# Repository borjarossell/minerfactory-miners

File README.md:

minerfactory-miners
===================
Minerfactory custom design Bitcoin ASIC miners using the BITFURY ASIC chip.
The project includes the Eagle CAD .brd and .sch board and schematic files for each board. No gerber files included.

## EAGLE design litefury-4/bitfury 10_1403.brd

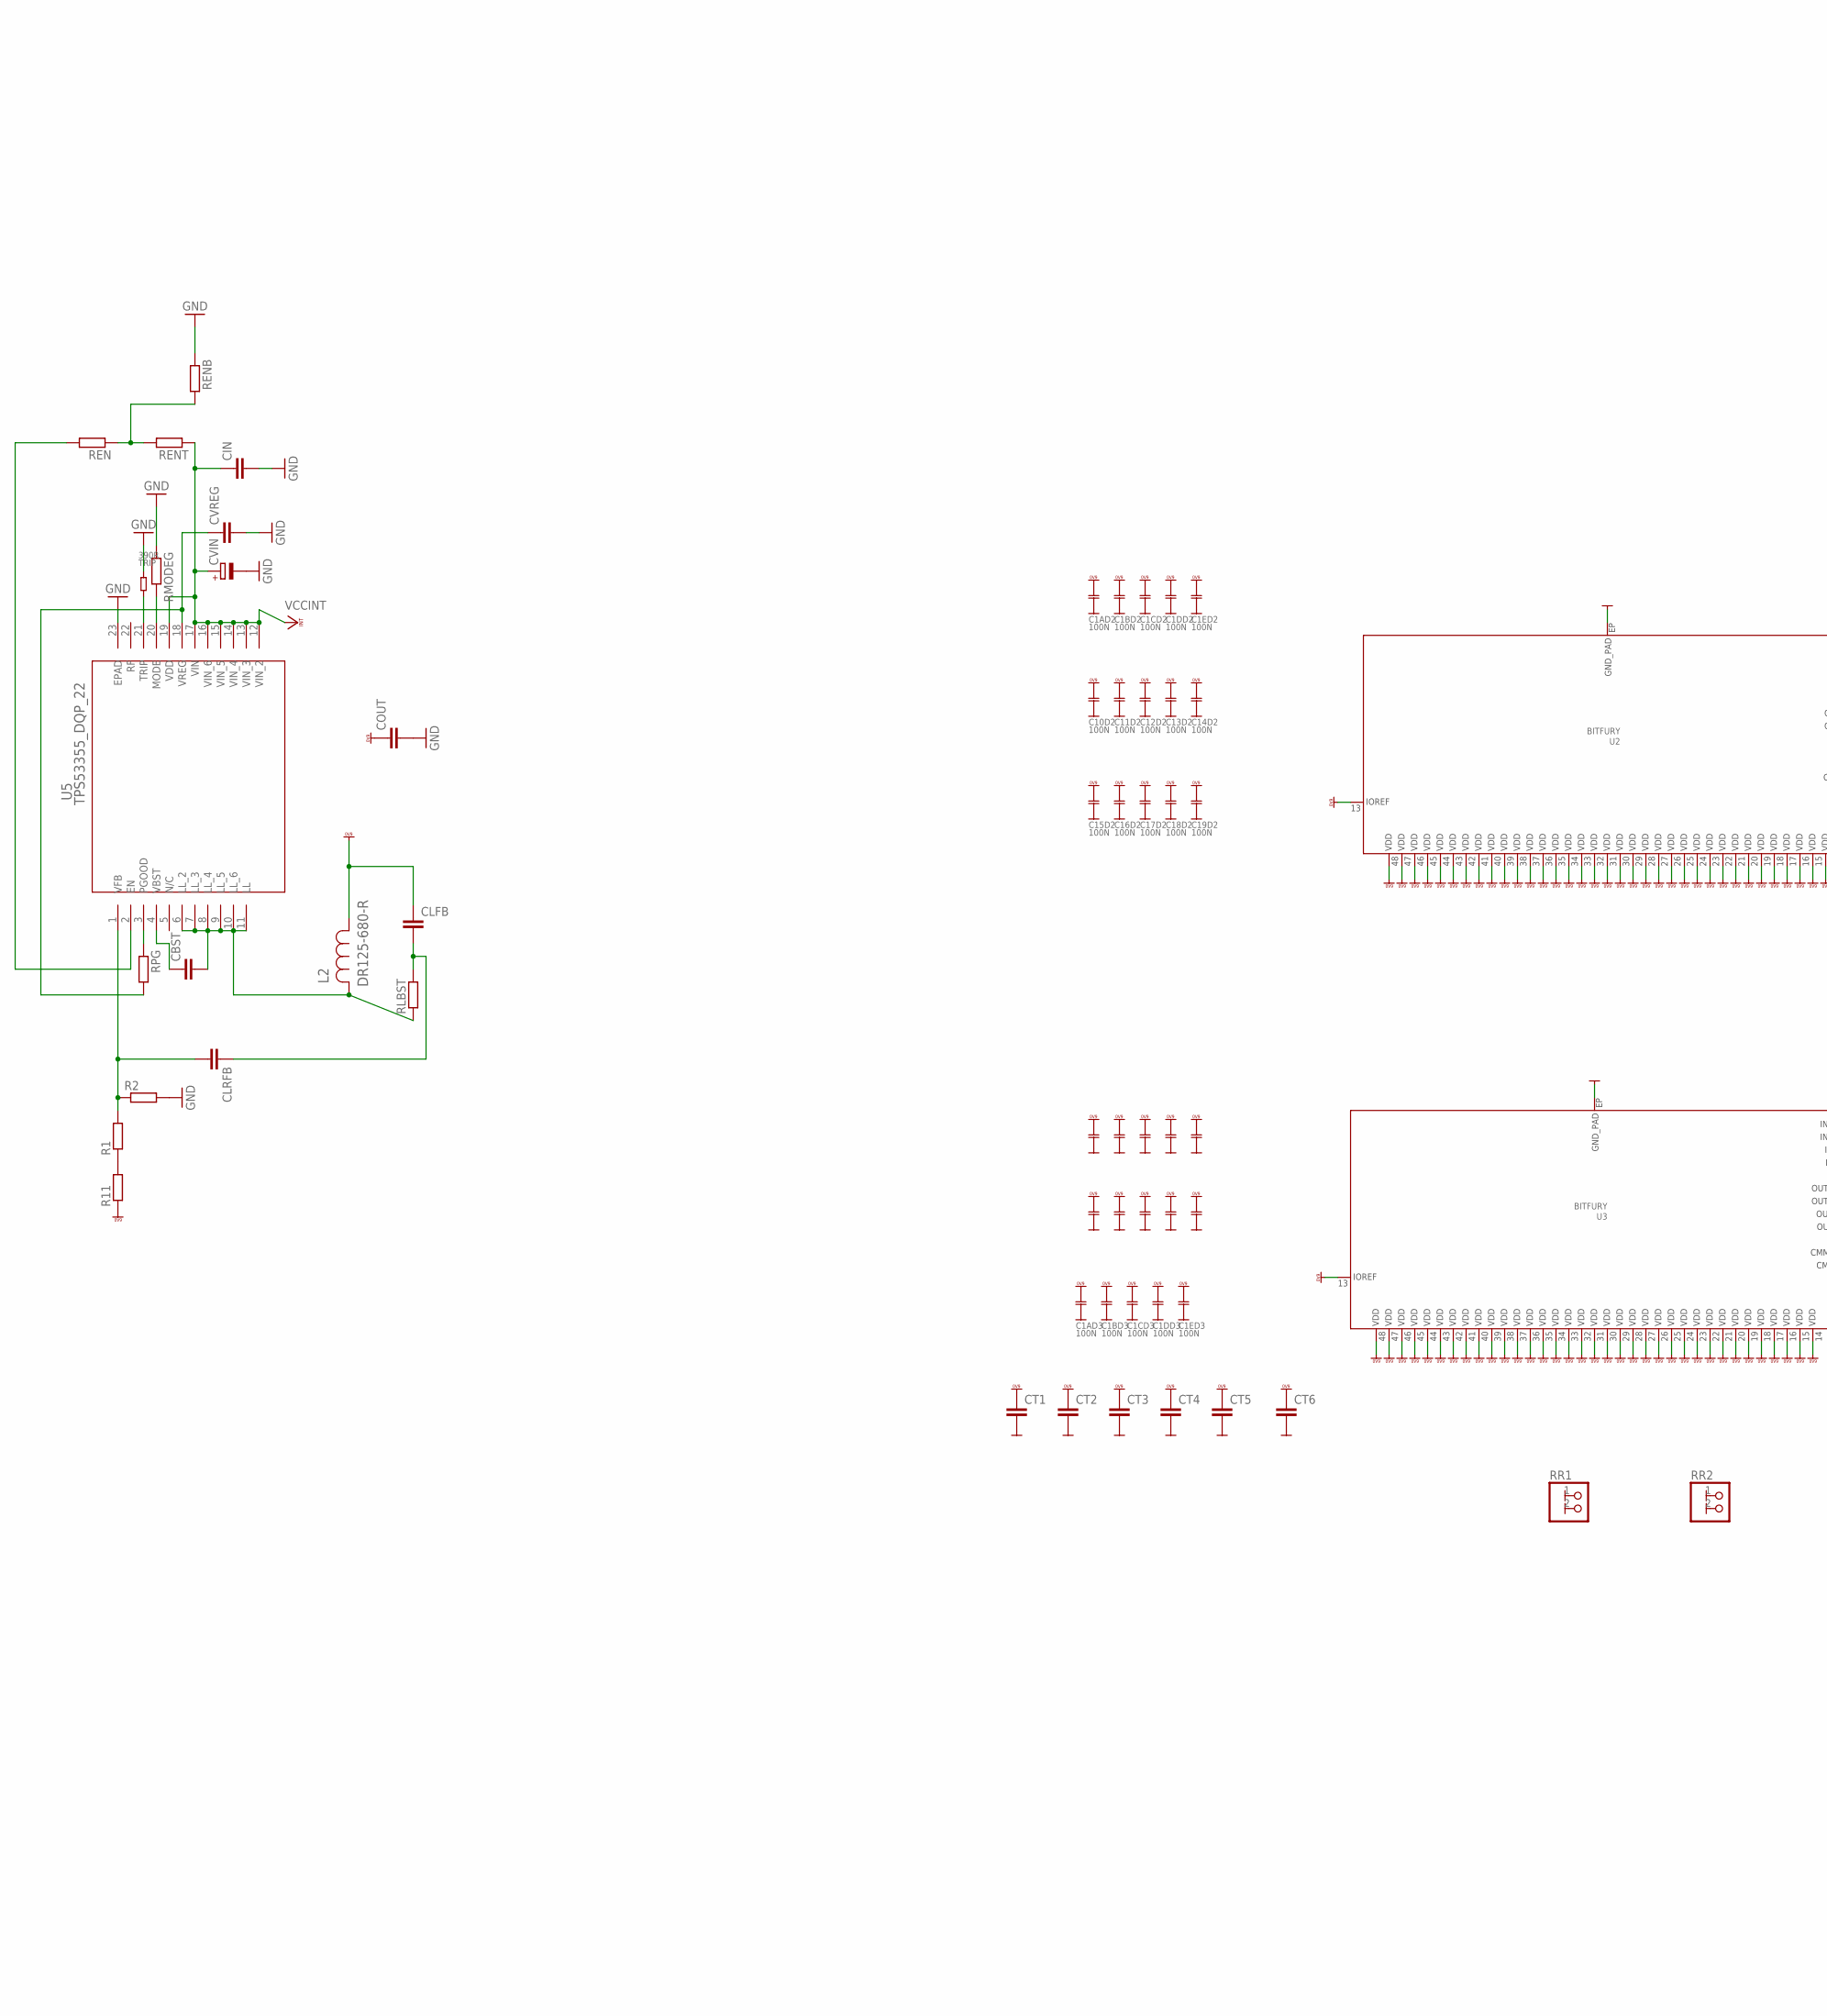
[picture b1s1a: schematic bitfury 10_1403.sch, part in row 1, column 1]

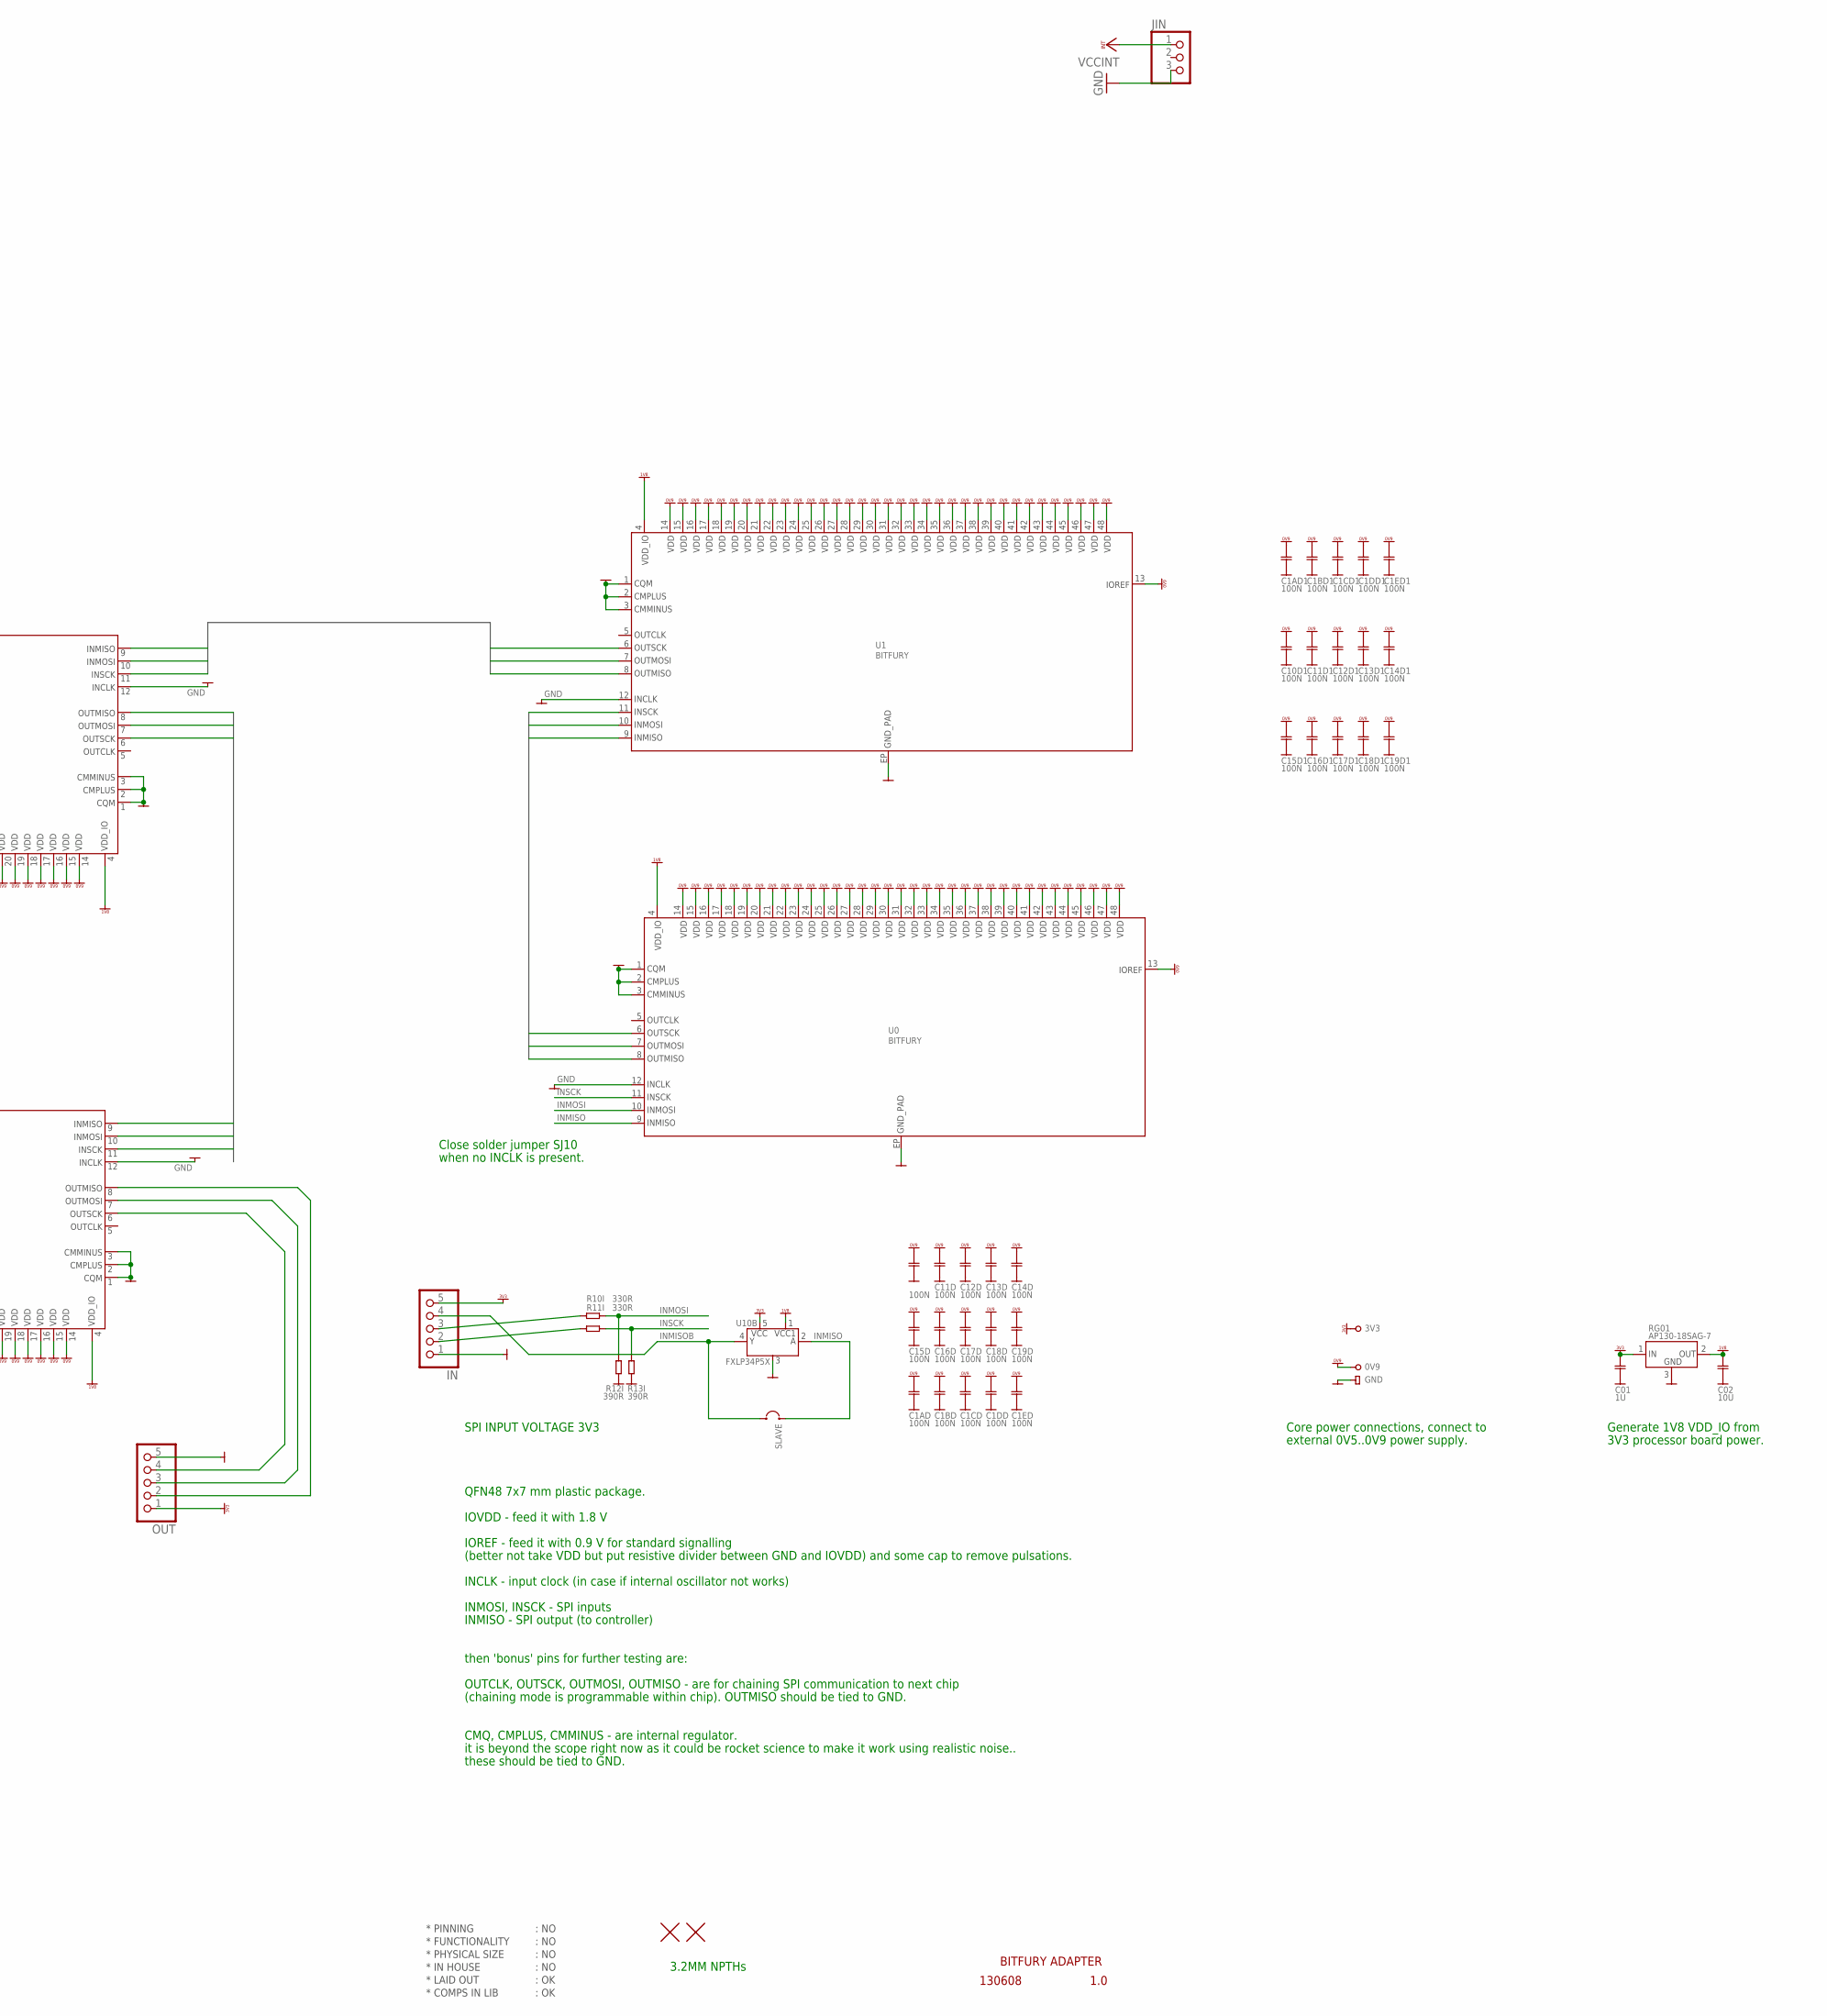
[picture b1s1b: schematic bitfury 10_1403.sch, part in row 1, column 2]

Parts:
0V9, 3V3: PIN_TEST_BIG; PAD_HOLE_BIG
C01: 1U; CAP0603
C1AD, C1AD1, C1AD2, C1AD3, C1BD, C1BD1, C1BD2, C1BD3, C1CD, C1CD1, C1CD2, C1CD3, C1DD, C1DD1, C1DD2, C1DD3, C1ED, C1ED1, C1ED2, C1ED3, C10D, C10D1, C10D2, C10D3, C11D, C11D1, C11D2, C11D3, C12D, C12D1, C12D2, C12D3, C13D, C13D1, C13D2, C13D3, C14D, C14D1, C14D2, C14D3, C15D, C15D1, C15D2, C15D3, C16D, C16D1, C16D2, C16D3, C17D, C17D1, C17D2, C17D3, C18D, C18D1, C18D2, C18D3, C19D, C19D1, C19D2, C19D3: 100N; CAP0402
C02: 10U; CAP0603
CBST: C-EUC0805; C0805
CIN: C-EUC1210; C1210
CLFB: C-EUC0805; C0805
CLRFB: C-EUC0805; C0805
COUT: C-EUC1210; C1210
CT1, CT2, CT3, CT4, CT5, CT6: C-EUC1206; C1206
CVIN: CPOL-EU153CLV-0505; 153CLV-0505
CVREG: C-EUC0603; C0603
H1, H2: HOLE_NPTH_3.2MM
IN: PINHD-1X5/90; 1X05/90
JIN: PINHD-1X3; 1X03
L2: DR125-680-R; INDM125125X600N
OUT: PINHD-1X5/90; 1X05/90
R1, R2, R11: R-EU_R0603; R0603
R10I, R11I: 330R; RES0603
R12I, R13I: 390R; RES0603
REN: R-EU_R0603; R0603
RENB: R-EU_R0603; R0603
RENT: R-EU_R0603; R0603
RG01: AP130-18SAG-7; SOT23
RLBST: R-EU_R0603; R0603
RMODEG: R-EU_R0603; R0603
RPG: R-EU_R0603; R0603
RR1, RR2: PINHD-1X2/90; 1X02/90
SLAVE: SJ2SJ2-S; SJ2-S
TRIP: 390R; RES0603
U0, U1, U2, U3: BITFURY; QNF48
U5: TPS53355_DQP_22; DQP22_5P479X3P24
U10B: FXLP34P5X; SOT23-5
U$83: PIN_GND; PAD_HOLE_SQR_1.8MM

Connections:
B1B2C1: U0.6 (6.OUTSCK), U1.11 (11.INSCK)
B1B2C2: U0.7 (7.OUTMOSI), U1.10 (10.INMOSI)
B1B2C3: U0.8 (8.OUTMISO), U1.9 (9.INMISO)
B2B3C1: U1.6 (6.OUTSCK), U2.11 (11.INSCK)
B2B3C2: U1.7 (7.OUTMOSI), U2.10 (10.INMOSI)
B2B3C3: U1.8 (8.OUTMISO), U2.9 (9.INMISO)
B3B4C1: U2.6 (6.OUTSCK), U3.11 (11.INSCK)
B3B4C2: U2.7 (7.OUTMOSI), U3.10 (10.INMOSI)
B3B4C3: U2.8 (8.OUTMISO), U3.9 (9.INMISO)
GND: C01.2, C1AD.2, C1AD1.2, C1AD2.2, C1AD3.2, C1BD.2, C1BD1.2, C1BD2.2, C1BD3.2, C1CD.2, C1CD1.2, C1CD2.2, C1CD3.2, C1DD.2, C1DD1.2, C1DD2.2, C1DD3.2, C1ED.2, C1ED1.2, C1ED2.2, C1ED3.2, C02.2, C10D.2, C10D1.2, C10D2.2, C10D3.2, C11D.2, C11D1.2, C11D2.2, C11D3.2, C12D.2, C12D1.2, C12D2.2, C12D3.2, C13D.2, C13D1.2, C13D2.2, C13D3.2, C14D.2, C14D1.2, C14D2.2, C14D3.2, C15D.2, C15D1.2, C15D2.2, C15D3.2, C16D.2, C16D1.2, C16D2.2, C16D3.2, C17D.2, C17D1.2, C17D2.2, C17D3.2, C18D.2, C18D1.2, C18D2.2, C18D3.2, C19D.2, C19D1.2, C19D2.2, C19D3.2, CIN.2, COUT.2, CT1.2, CT2.2, CT3.2, CT4.2, CT5.2, CT6.2, CVIN.-, CVREG.2, IN.1, JIN.3, OUT.5, R2.2, R12I.1, R13I.1, RENB.1, RG01.3 (3.GND), RMODEG.1, RR1.1, RR1.2, RR2.1, RR2.2, TRIP.1, U0.1 (1.QCM), U0.2 (2.CMPLUS), U0.3 (3.CMMINUS), U0.12 (12.INCLK), U0.EP (EP.VSS_EP), U0.V1 (EP.VSS_EP), U0.V2 (EP.VSS_EP), U0.V3 (EP.VSS_EP), U0.V4 (EP.VSS_EP), U0.V5 (EP.VSS_EP), U0.V6 (EP.VSS_EP), U0.V7 (EP.VSS_EP), U0.V8 (EP.VSS_EP), U0.V9 (EP.VSS_EP), U0.V10 (EP.VSS_EP), U0.V11 (EP.VSS_EP), U0.V12 (EP.VSS_EP), U0.V13 (EP.VSS_EP), U0.V14 (EP.VSS_EP), U0.V15 (EP.VSS_EP), U0.V16 (EP.VSS_EP), U0.V17 (EP.VSS_EP), U0.V18 (EP.VSS_EP), U0.V19 (EP.VSS_EP), U0.V20 (EP.VSS_EP), U0.V21 (EP.VSS_EP), U0.V22 (EP.VSS_EP), U0.V23 (EP.VSS_EP), U0.V24 (EP.VSS_EP), U0.V25 (EP.VSS_EP), U1.1 (1.QCM), U1.2 (2.CMPLUS), U1.3 (3.CMMINUS), U1.12 (12.INCLK), U1.EP (EP.VSS_EP), U1.V1 (EP.VSS_EP), U1.V2 (EP.VSS_EP), U1.V3 (EP.VSS_EP), U1.V4 (EP.VSS_EP), U1.V5 (EP.VSS_EP), U1.V6 (EP.VSS_EP), U1.V7 (EP.VSS_EP), U1.V8 (EP.VSS_EP), U1.V9 (EP.VSS_EP), U1.V10 (EP.VSS_EP), U1.V11 (EP.VSS_EP), U1.V12 (EP.VSS_EP), U1.V13 (EP.VSS_EP), U1.V14 (EP.VSS_EP), U1.V15 (EP.VSS_EP), U1.V16 (EP.VSS_EP), U1.V17 (EP.VSS_EP), U1.V18 (EP.VSS_EP), U1.V19 (EP.VSS_EP), U1.V20 (EP.VSS_EP), U1.V21 (EP.VSS_EP), U1.V22 (EP.VSS_EP), U1.V23 (EP.VSS_EP), U1.V24 (EP.VSS_EP), U1.V25 (EP.VSS_EP), U2.1 (1.QCM), U2.2 (2.CMPLUS), U2.3 (3.CMMINUS), U2.12 (12.INCLK), U2.EP (EP.VSS_EP), U2.V1 (EP.VSS_EP), U2.V2 (EP.VSS_EP), U2.V3 (EP.VSS_EP), U2.V4 (EP.VSS_EP), U2.V5 (EP.VSS_EP), U2.V6 (EP.VSS_EP), U2.V7 (EP.VSS_EP), U2.V8 (EP.VSS_EP), U2.V9 (EP.VSS_EP), U2.V10 (EP.VSS_EP)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
INMISO: SLAVE.2, U0.9 (9.INMISO), U10B.2 (2.A)
INMISOB: IN.4, SLAVE.1, U10B.4 (4.Y)
INMOSI: R10I.2, R12I.2, U0.10 (10.INMOSI)
INSCK: R11I.2, R13I.2, U0.11 (11.INSCK)
unnamed: IN.2, R11I.1
unnamed: IN.3, R10I.1
unnamed: OUT.3, U3.7 (7.OUTMOSI)
unnamed: OUT.4, U3.6 (6.OUTSCK)
unnamed: CLFB.2, CLRFB.1, RLBST.2
unnamed: CLRFB.2, R1.2, R2.1, U5.1 (VFB)
unnamed: R1.1, R11.2
unnamed: REN.2, U5.2 (EN)
unnamed: REN.1, RENB.2, RENT.2
unnamed: CVREG.1, RPG.2, U5.18 (VREG)
unnamed: TRIP.2, U5.21 (TRIP)
unnamed: RPG.1, U5.3 (PGOOD)
unnamed: OUT.2, U3.8 (8.OUTMISO)
unnamed: RMODEG.2, U5.20 (MODE)
unnamed: CBST.1, U5.4 (VBST)
unnamed: CBST.2, L2.2, RLBST.1, U5.6 (LL_2), U5.7 (LL_3), U5.8 (LL_4), U5.9 (LL_5), U5.10 (LL_6), U5.11 (LL)
VCCINT: CIN.1, CVIN.+, JIN.1, RENT.1, U5.12 (VIN_2), U5.13 (VIN_3), U5.14 (VIN_4), U5.15 (VIN_5), U5.16 (VIN_6), U5.17 (VIN), U5.19 (VDD)
VDD_0V9: 0V9.1, C1AD.1, C1AD1.1, C1AD2.1, C1AD3.1, C1BD.1, C1BD1.1, C1BD2.1, C1BD3.1, C1CD.1, C1CD1.1, C1CD2.1, C1CD3.1, C1DD.1, C1DD1.1, C1DD2.1, C1DD3.1, C1ED.1, C1ED1.1, C1ED2.1, C1ED3.1, C10D.1, C10D1.1, C10D2.1, C10D3.1, C11D.1, C11D1.1, C11D2.1, C11D3.1, C12D.1, C12D1.1, C12D2.1, C12D3.1, C13D.1, C13D1.1, C13D2.1, C13D3.1, C14D.1, C14D1.1, C14D2.1, C14D3.1, C15D.1, C15D1.1, C15D2.1, C15D3.1, C16D.1, C16D1.1, C16D2.1, C16D3.1, C17D.1, C17D1.1, C17D2.1, C17D3.1, C18D.1, C18D1.1, C18D2.1, C18D3.1, C19D.1, C19D1.1, C19D2.1, C19D3.1, CLFB.1, COUT.1, CT1.1, CT2.1, CT3.1, CT4.1, CT5.1, CT6.1, L2.1, R11.1, U0.13 (13.IOREF), U0.14 (14.VDD), U0.15 (15.VDD), U0.16 (16.VDD), U0.17 (17.VDD), U0.18 (18.VDD), U0.19 (19.VDD), U0.20 (20.VDD), U0.21 (21.VDD), U0.22 (22.VDD), U0.23 (23.VDD), U0.24 (24.VDD), U0.25 (25.VDD), U0.26 (26.VDD), U0.27 (27.VDD), U0.28 (28.VDD), U0.29 (29.VDD), U0.30 (30.VDD), U0.31 (31.VDD), U0.32 (32.VDD), U0.33 (33.VDD), U0.34 (34.VDD), U0.35 (35.VDD), U0.36 (36.VDD), U0.37 (37.VDD), U0.38 (38.VDD), U0.39 (39.VDD), U0.40 (40.VDD), U0.41 (41.VDD), U0.42 (42.VDD), U0.43 (43.VDD), U0.44 (44.VDD), U0.45 (45.VDD), U0.46 (46.VDD), U0.47 (47.VDD), U0.48 (48.VDD), U1.13 (13.IOREF), U1.14 (14.VDD), U1.15 (15.VDD), U1.16 (16.VDD), U1.17 (17.VDD), U1.18 (18.VDD), U1.19 (19.VDD), U1.20 (20.VDD), U1.21 (21.VDD), U1.22 (22.VDD), U1.23 (23.VDD), U1.24 (24.VDD), U1.25 (25.VDD), U1.26 (26.VDD), U1.27 (27.VDD), U1.28 (28.VDD), U1.29 (29.VDD), U1.30 (30.VDD), U1.31 (31.VDD), U1.32 (32.VDD), U1.33 (33.VDD), U1.34 (34.VDD), U1.35 (35.VDD), U1.36 (36.VDD), U1.37 (37.VDD), U1.38 (38.VDD), U1.39 (39.VDD), U1.40 (40.VDD), U1.41 (41.VDD), U1.42 (42.VDD), U1.43 (43.VDD), U1.44 (44.VDD), U1.45 (45.VDD), U1.46 (46.VDD), U1.47 (47.VDD), U1.48 (48.VDD), U2.13 (13.IOREF), U2.14 (14.VDD), U2.15 (15.VDD), U2.16 (16.VDD), U2.17 (17.VDD), U2.18 (18.VDD), U2.19 (19.VDD), U2.20 (20.VDD), U2.21 (21.VDD), U2.22 (22.VDD), U2.23 (23.VDD), U2.24 (24.VDD), U2.25 (25.VDD), U2.26 (26.VDD), U2.27 (27.VDD), U2.28 (28.VDD), U2.29 (29.VDD), U2.30 (30.VDD)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
VDD_1V8: C02.1, RG01.2 (2.OUT), U0.4 (4.VDD_IO), U1.4 (4.VDD_IO), U2.4 (4.VDD_IO), U3.4 (4.VDD_IO), U10B.1 (1.VCC1)
VDD_3V3: 3V3.1, C01.1, IN.5, OUT.1, RG01.1 (1.IN), U10B.5 (5.VCC)

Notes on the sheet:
* PINNING
* FUNCTIONALITY
* PHYSICAL SIZE
* LAID OUT
* COMPS IN LIB
* IN HOUSE
: NO
BITFURY ADAPTER
130608
1.0
: OK
QFN48 7x7 mm plastic package.
IOVDD - feed it with 1.8 V
IOREF - feed it with 0.9 V for standard signalling
(better not take VDD but put resistive divider between GND and IOVDD) and some cap to remove pulsations.
INCLK - input clock (in case if internal oscillator not works)
INMOSI, INSCK - SPI inputs
INMISO - SPI output (to controller)
then 'bonus' pins for further testing are:
OUTCLK, OUTSCK, OUTMOSI, OUTMISO - are for chaining SPI communication to next chip
CMQ, CMPLUS, CMMINUS - are internal regulator.
it is beyond the scope right now as it could be rocket science to make it work using realistic noise..
these should be tied to GND.
Generate 1V8 VDD_IO from
3V3 processor board power.
(chaining mode is programmable within chip). OUTMISO should be tied to GND.
3.2MM NPTHs
Close solder jumper SJ10
when no INCLK is present.
Core power connections, connect to
GND
external 0V5..0V9 power supply.
SPI INPUT VOLTAGE 3V3

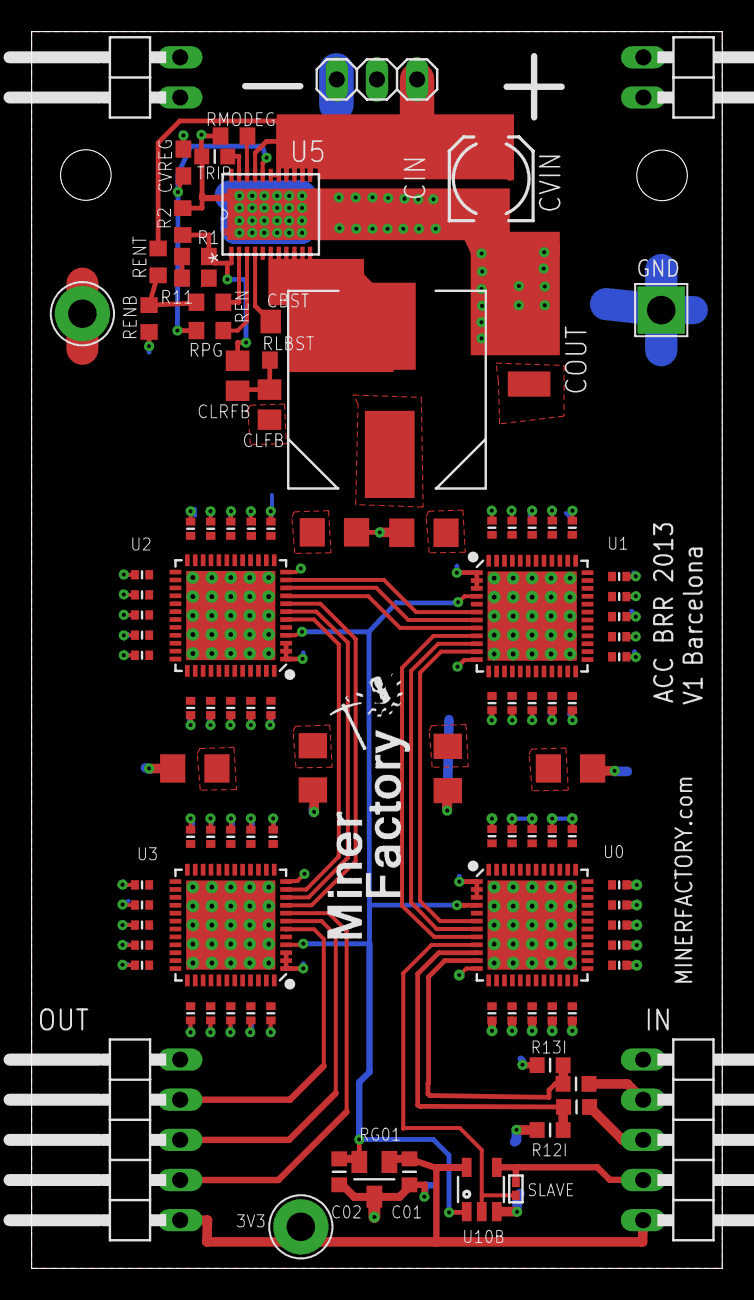
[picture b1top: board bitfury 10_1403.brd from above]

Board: 2 copper layers, 43.7 x 78.2 mm, 109 parts (0 on the bottom side), 34 nets.

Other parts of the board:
U$133: MINERFACTORY

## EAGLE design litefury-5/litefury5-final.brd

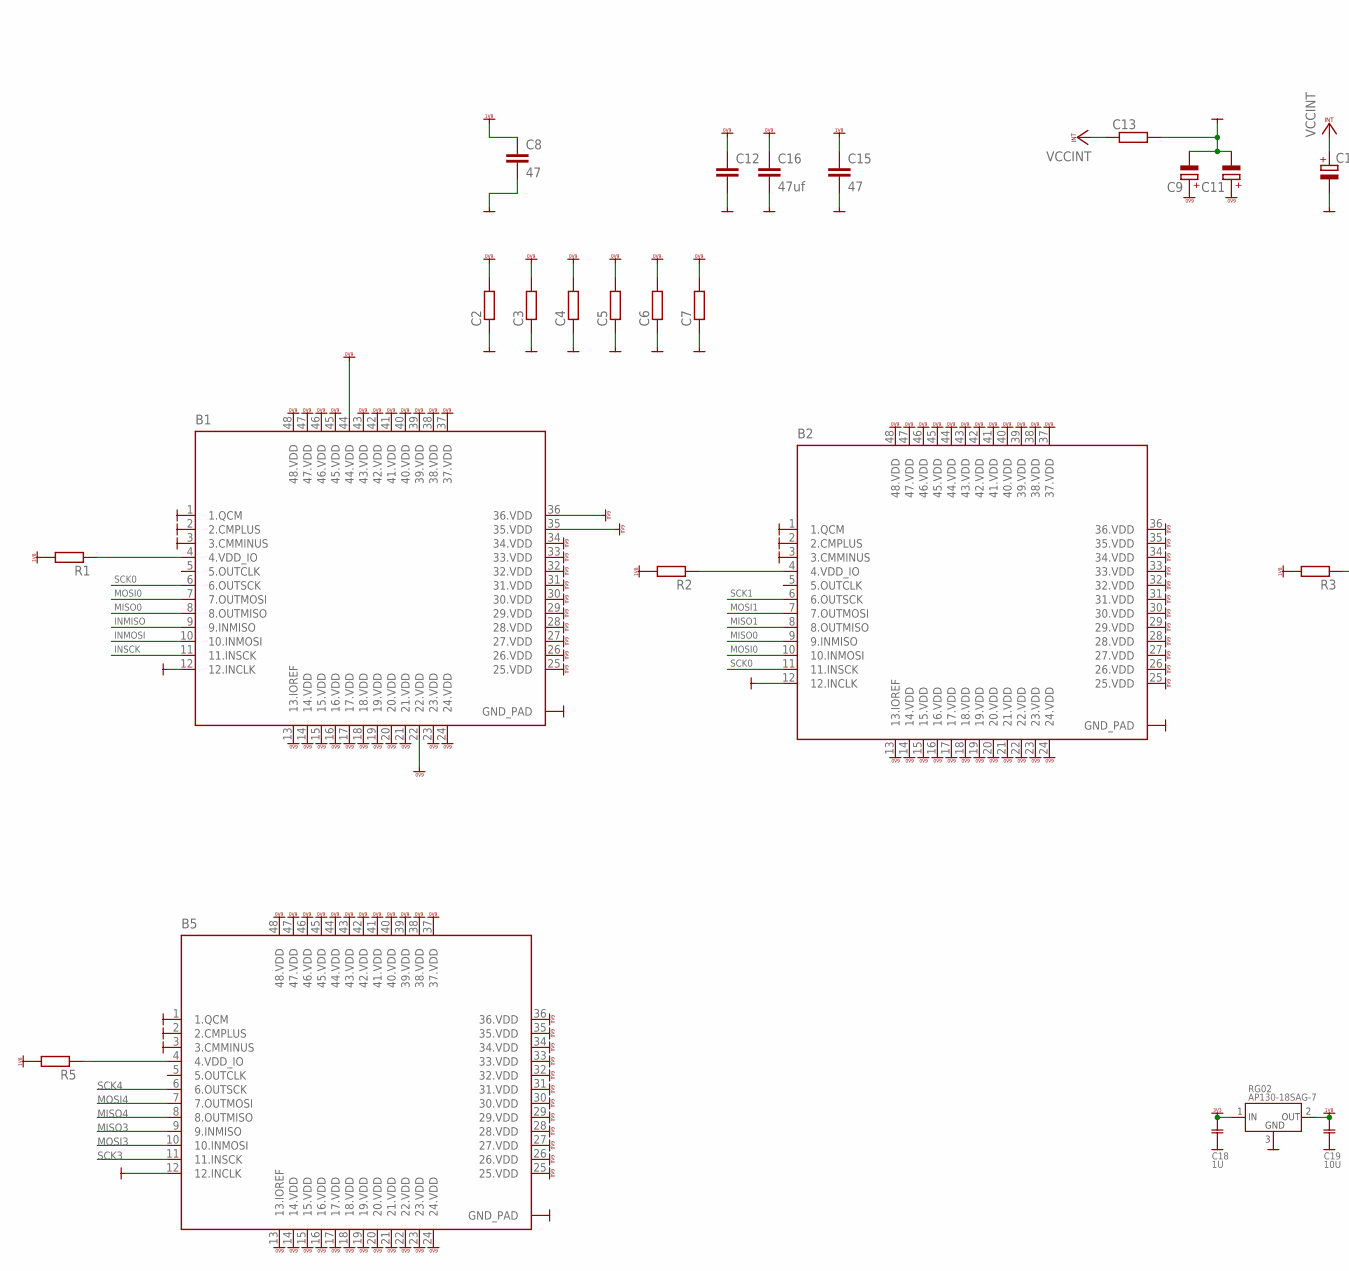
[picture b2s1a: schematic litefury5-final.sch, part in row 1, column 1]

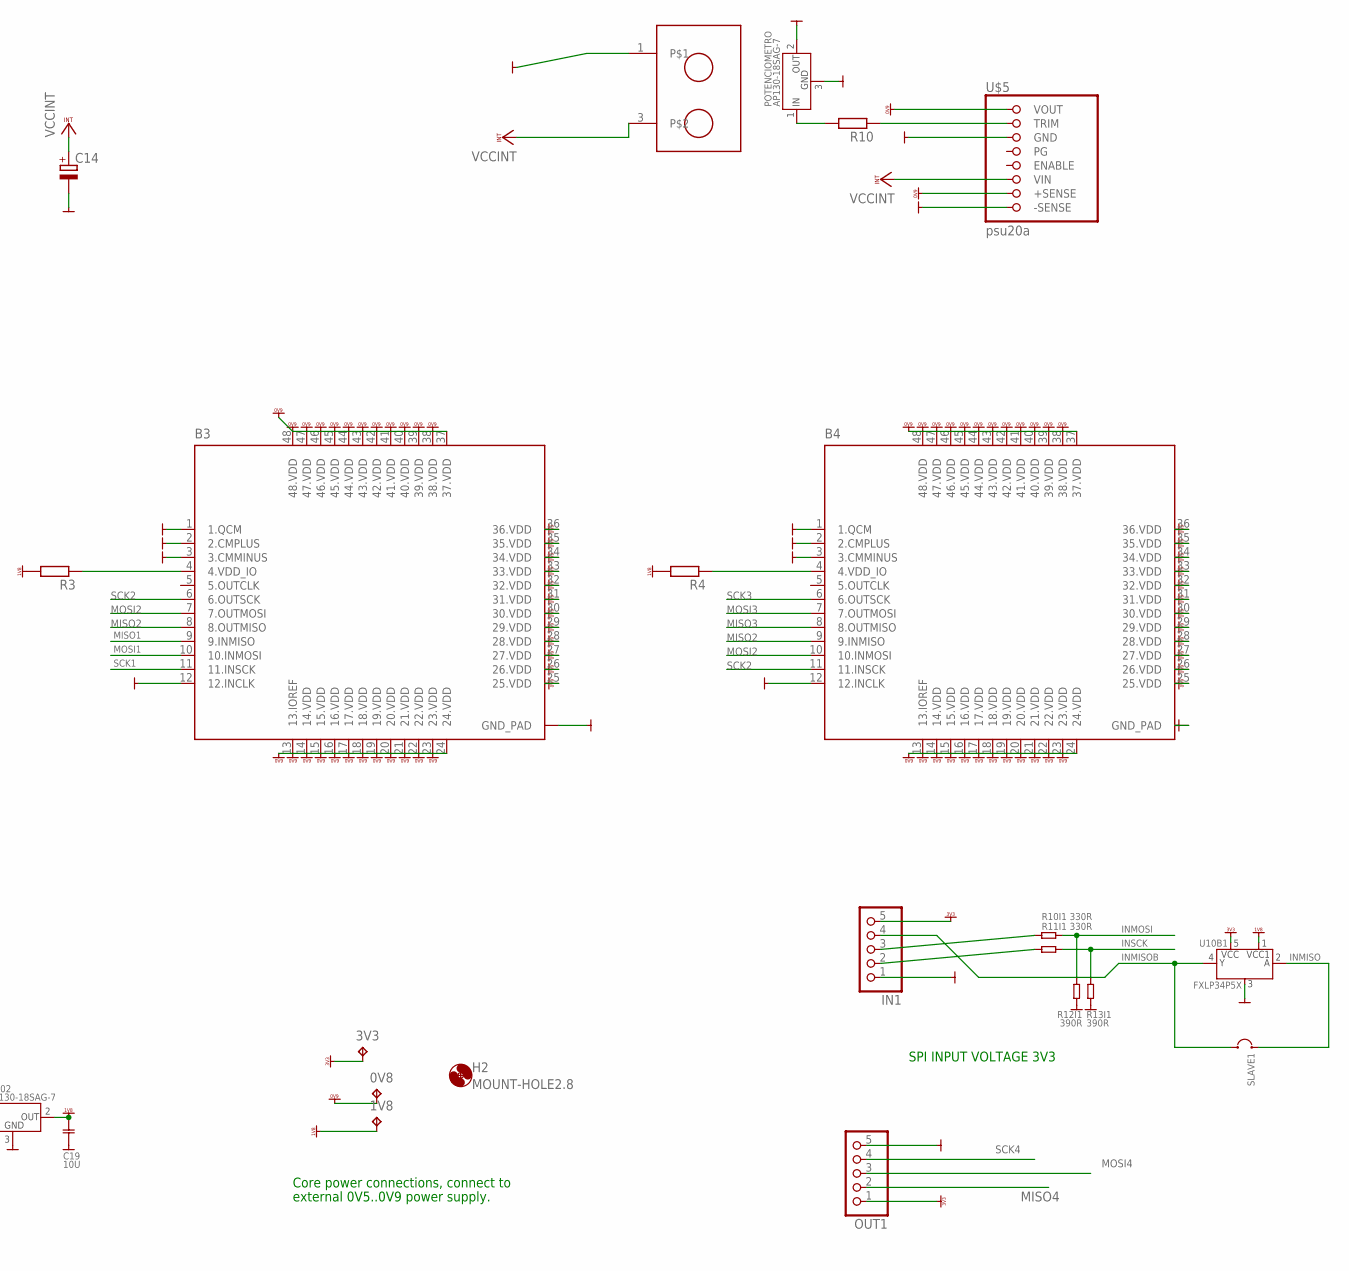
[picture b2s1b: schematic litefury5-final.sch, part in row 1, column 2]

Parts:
0V8, 3V3: TPTP14SQ; TP14SQ
1V8: TPTP10SQ; TP10SQ
B1, B2, B3, B4, B5: BITFURYM; QFN48
C2, C3, C4, C5, C6, C7, C13: RR2010; R2010
C8, C15: 47; C1210
C9, C11, C14: CPOL-EUCT7343; CT7343
C12: CC1210; C1210
C16: 47uf; C1210
C18: 1U; CAP0603
C19: 10U; CAP0603
H2: MOUNT-HOLE2.8; 2,8
IN1: PINHD-1X5/90; 1X05/90
OUT1: PINHD-1X5/90; 1X05/90
POTENCIOMETRO: AP130-18SAG-7; SOT23
R1, R2, R3, R4, R5: R-EU_R1206; R1206
R10: RR0603; R0603
R10I1, R11I1: 330R; RES0603
R12I1, R13I1: 390R; RES0603
RG02: AP130-18SAG-7; SOT23
SLAVE1: SJ2SJ2-S; SJ2-S
U10B1: FXLP34P5X; SOT23-5
U$5: D12S05020; PSU20A
U$6: RTORNILLO; REGLETATORNILLO

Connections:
GND: B1.1 (1.QCM), B1.2 (2.CMPLUS), B1.3 (3.CMMINUS), B1.12 (12.INCLK), B1.EXP (GND_PAD), B1.P$1 (GND_PAD), B1.P$2 (GND_PAD), B1.P$3 (GND_PAD), B1.P$4 (GND_PAD), B1.P$5 (GND_PAD), B1.P$6 (GND_PAD), B1.P$7 (GND_PAD), B1.P$8 (GND_PAD), B1.P$9 (GND_PAD), B1.P$10 (GND_PAD), B1.P$11 (GND_PAD), B1.P$12 (GND_PAD), B1.P$13 (GND_PAD), B1.P$14 (GND_PAD), B1.P$15 (GND_PAD), B1.P$16 (GND_PAD), B1.P$17 (GND_PAD), B1.P$18 (GND_PAD), B1.P$19 (GND_PAD), B1.P$20 (GND_PAD), B1.P$21 (GND_PAD), B1.P$22 (GND_PAD), B1.P$23 (GND_PAD), B1.P$24 (GND_PAD), B1.P$25 (GND_PAD), B2.1 (1.QCM), B2.2 (2.CMPLUS), B2.3 (3.CMMINUS), B2.12 (12.INCLK), B2.EXP (GND_PAD), B2.P$1 (GND_PAD), B2.P$2 (GND_PAD), B2.P$3 (GND_PAD), B2.P$4 (GND_PAD), B2.P$5 (GND_PAD), B2.P$6 (GND_PAD), B2.P$7 (GND_PAD), B2.P$8 (GND_PAD), B2.P$9 (GND_PAD), B2.P$10 (GND_PAD), B2.P$11 (GND_PAD), B2.P$12 (GND_PAD), B2.P$13 (GND_PAD), B2.P$14 (GND_PAD), B2.P$15 (GND_PAD), B2.P$16 (GND_PAD), B2.P$17 (GND_PAD), B2.P$18 (GND_PAD), B2.P$19 (GND_PAD), B2.P$20 (GND_PAD), B2.P$21 (GND_PAD), B2.P$22 (GND_PAD), B2.P$23 (GND_PAD), B2.P$24 (GND_PAD), B2.P$25 (GND_PAD), B3.1 (1.QCM), B3.2 (2.CMPLUS), B3.3 (3.CMMINUS), B3.12 (12.INCLK), B3.EXP (GND_PAD), B3.P$1 (GND_PAD), B3.P$2 (GND_PAD), B3.P$3 (GND_PAD), B3.P$4 (GND_PAD), B3.P$5 (GND_PAD), B3.P$6 (GND_PAD), B3.P$7 (GND_PAD), B3.P$8 (GND_PAD), B3.P$9 (GND_PAD), B3.P$10 (GND_PAD), B3.P$11 (GND_PAD), B3.P$12 (GND_PAD), B3.P$13 (GND_PAD), B3.P$14 (GND_PAD), B3.P$15 (GND_PAD), B3.P$16 (GND_PAD), B3.P$17 (GND_PAD), B3.P$18 (GND_PAD), B3.P$19 (GND_PAD), B3.P$20 (GND_PAD), B3.P$21 (GND_PAD), B3.P$22 (GND_PAD), B3.P$23 (GND_PAD), B3.P$24 (GND_PAD), B3.P$25 (GND_PAD), B4.1 (1.QCM), B4.2 (2.CMPLUS), B4.3 (3.CMMINUS), B4.12 (12.INCLK), B4.EXP (GND_PAD), B4.P$1 (GND_PAD), B4.P$2 (GND_PAD), B4.P$3 (GND_PAD), B4.P$4 (GND_PAD), B4.P$5 (GND_PAD), B4.P$6 (GND_PAD), B4.P$7 (GND_PAD), B4.P$8 (GND_PAD), B4.P$9 (GND_PAD), B4.P$10 (GND_PAD), B4.P$11 (GND_PAD), B4.P$12 (GND_PAD), B4.P$13 (GND_PAD), B4.P$14 (GND_PAD), B4.P$15 (GND_PAD), B4.P$16 (GND_PAD), B4.P$17 (GND_PAD), B4.P$18 (GND_PAD), B4.P$19 (GND_PAD), B4.P$20 (GND_PAD), B4.P$21 (GND_PAD), B4.P$22 (GND_PAD), B4.P$23 (GND_PAD), B4.P$24 (GND_PAD), B4.P$25 (GND_PAD), B5.1 (1.QCM), B5.2 (2.CMPLUS), B5.3 (3.CMMINUS), B5.12 (12.INCLK), B5.EXP (GND_PAD), B5.P$1 (GND_PAD), B5.P$2 (GND_PAD), B5.P$3 (GND_PAD), B5.P$4 (GND_PAD), B5.P$5 (GND_PAD), B5.P$6 (GND_PAD), B5.P$7 (GND_PAD), B5.P$8 (GND_PAD), B5.P$9 (GND_PAD), B5.P$10 (GND_PAD), B5.P$11 (GND_PAD), B5.P$12 (GND_PAD), B5.P$13 (GND_PAD), B5.P$14 (GND_PAD), B5.P$15 (GND_PAD), B5.P$16 (GND_PAD), B5.P$17 (GND_PAD), B5.P$18 (GND_PAD), B5.P$19 (GND_PAD), B5.P$20 (GND_PAD), B5.P$21 (GND_PAD), B5.P$22 (GND_PAD), B5.P$23 (GND_PAD), B5.P$24 (GND_PAD), B5.P$25 (GND_PAD), C2.1, C3.1, C4.1, C5.1, C6.1, C7.1, C8.2, C9.-, C11.-, C12.2, C13.2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
INMISO: B1.9 (9.INMISO), SLAVE1.2, U10B1.2 (2.A)
INMISOB: IN1.4, SLAVE1.1, U10B1.4 (4.Y)
INMOSI: B1.10 (10.INMOSI), R10I1.2, R12I1.2
INSCK: B1.11 (11.INSCK), R11I1.2, R13I1.2
MISO0: B1.8 (8.OUTMISO), B2.9 (9.INMISO)
MISO1: B2.8 (8.OUTMISO), B3.9 (9.INMISO)
MISO2: B3.8 (8.OUTMISO), B4.9 (9.INMISO)
MISO3: B4.8 (8.OUTMISO), B5.9 (9.INMISO)
MISO4: B5.8 (8.OUTMISO), OUT1.2
MOSI0: B1.7 (7.OUTMOSI), B2.10 (10.INMOSI)
MOSI1: B2.7 (7.OUTMOSI), B3.10 (10.INMOSI)
MOSI2: B3.7 (7.OUTMOSI), B4.10 (10.INMOSI)
MOSI3: B4.7 (7.OUTMOSI), B5.10 (10.INMOSI)
MOSI4: B5.7 (7.OUTMOSI), OUT1.3
unnamed: B1.4 (4.VDD_IO), R1.1
unnamed: B2.4 (4.VDD_IO), R2.1
unnamed: B3.4 (4.VDD_IO), R3.1
unnamed: B4.4 (4.VDD_IO), R4.1
unnamed: B5.4 (4.VDD_IO), R5.1
unnamed: POTENCIOMETRO.1 (1.IN), R10.2
unnamed: R10.1, U$5.2 (TRIM)
unnamed: IN1.2, R11I1.1
unnamed: IN1.3, R10I1.1
SCK0: B1.6 (6.OUTSCK), B2.11 (11.INSCK)
SCK1: B2.6 (6.OUTSCK), B3.11 (11.INSCK)
SCK2: B3.6 (6.OUTSCK), B4.11 (11.INSCK)
SCK3: B4.6 (6.OUTSCK), B5.11 (11.INSCK)
SCK4: B5.6 (6.OUTSCK), OUT1.4
VCCINT: C13.1, C14.+, U$5.6 (VIN), U$6.3
VDD_0V9: 0V8.TP, B1.13 (13.IOREF), B1.14 (14.VDD), B1.15 (15.VDD), B1.16 (16.VDD), B1.17 (17.VDD), B1.18 (18.VDD), B1.19 (19.VDD), B1.20 (20.VDD), B1.21 (21.VDD), B1.22 (22.VDD), B1.23 (23.VDD), B1.24 (24.VDD), B1.25 (25.VDD), B1.26 (26.VDD), B1.27 (27.VDD), B1.28 (28.VDD), B1.29 (29.VDD), B1.30 (30.VDD), B1.31 (31.VDD), B1.32 (32.VDD), B1.33 (33.VDD), B1.34 (34.VDD), B1.35 (35.VDD), B1.36 (36.VDD), B1.37 (37.VDD), B1.38 (38.VDD), B1.39 (39.VDD), B1.40 (40.VDD), B1.41 (41.VDD), B1.42 (42.VDD), B1.43 (43.VDD), B1.44 (44.VDD), B1.45 (45.VDD), B1.46 (46.VDD), B1.47 (47.VDD), B1.48 (48.VDD), B2.13 (13.IOREF), B2.14 (14.VDD), B2.15 (15.VDD), B2.16 (16.VDD), B2.17 (17.VDD), B2.18 (18.VDD), B2.19 (19.VDD), B2.20 (20.VDD), B2.21 (21.VDD), B2.22 (22.VDD), B2.23 (23.VDD), B2.24 (24.VDD), B2.25 (25.VDD), B2.26 (26.VDD), B2.27 (27.VDD), B2.28 (28.VDD), B2.29 (29.VDD), B2.30 (30.VDD), B2.31 (31.VDD), B2.32 (32.VDD), B2.33 (33.VDD), B2.34 (34.VDD), B2.35 (35.VDD), B2.36 (36.VDD), B2.37 (37.VDD), B2.38 (38.VDD), B2.39 (39.VDD), B2.40 (40.VDD), B2.41 (41.VDD), B2.42 (42.VDD), B2.43 (43.VDD), B2.44 (44.VDD), B2.45 (45.VDD), B2.46 (46.VDD), B2.47 (47.VDD), B2.48 (48.VDD), B3.13 (13.IOREF), B3.14 (14.VDD), B3.15 (15.VDD), B3.16 (16.VDD), B3.17 (17.VDD), B3.18 (18.VDD), B3.19 (19.VDD), B3.20 (20.VDD), B3.21 (21.VDD), B3.22 (22.VDD), B3.23 (23.VDD), B3.24 (24.VDD), B3.25 (25.VDD), B3.26 (26.VDD), B3.27 (27.VDD), B3.28 (28.VDD), B3.29 (29.VDD), B3.30 (30.VDD), B3.31 (31.VDD), B3.32 (32.VDD), B3.33 (33.VDD), B3.34 (34.VDD), B3.35 (35.VDD), B3.36 (36.VDD), B3.37 (37.VDD), B3.38 (38.VDD), B3.39 (39.VDD), B3.40 (40.VDD), B3.41 (41.VDD), B3.42 (42.VDD), B3.43 (43.VDD), B3.44 (44.VDD), B3.45 (45.VDD), B3.46 (46.VDD), B3.47 (47.VDD), B3.48 (48.VDD), B4.13 (13.IOREF), B4.14 (14.VDD), B4.15 (15.VDD), B4.16 (16.VDD), B4.17 (17.VDD), B4.18 (18.VDD), B4.19 (19.VDD), B4.20 (20.VDD), B4.21 (21.VDD), B4.22 (22.VDD), B4.23 (23.VDD), B4.24 (24.VDD), B4.25 (25.VDD), B4.26 (26.VDD), B4.27 (27.VDD), B4.28 (28.VDD), B4.29 (29.VDD), B4.30 (30.VDD), B4.31 (31.VDD), B4.32 (32.VDD), B4.33 (33.VDD), B4.34 (34.VDD), B4.35 (35.VDD), B4.36 (36.VDD), B4.37 (37.VDD), B4.38 (38.VDD), B4.39 (39.VDD), B4.40 (40.VDD), B4.41 (41.VDD), B4.42 (42.VDD), B4.43 (43.VDD), B4.44 (44.VDD), B4.45 (45.VDD), B4.46 (46.VDD), B4.47 (47.VDD), B4.48 (48.VDD), B5.13 (13.IOREF), B5.14 (14.VDD), B5.15 (15.VDD), B5.16 (16.VDD), B5.17 (17.VDD), B5.18 (18.VDD), B5.19 (19.VDD), B5.20 (20.VDD), B5.21 (21.VDD), B5.22 (22.VDD), B5.23 (23.VDD), B5.24 (24.VDD), B5.25 (25.VDD), B5.26 (26.VDD), B5.27 (27.VDD), B5.28 (28.VDD)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
VDD_1V8: 1V8.TP, C8.1, C15.1, C19.1, R1.2, R2.2, R3.2, R4.2, R5.2, RG02.2 (2.OUT), U10B1.1 (1.VCC1)
VDD_3V3: 3V3.TP, C18.1, IN1.5, OUT1.1, RG02.1 (1.IN), U10B1.5 (5.VCC)

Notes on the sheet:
Core power connections, connect to
external 0V5..0V9 power supply.
SPI INPUT VOLTAGE 3V3

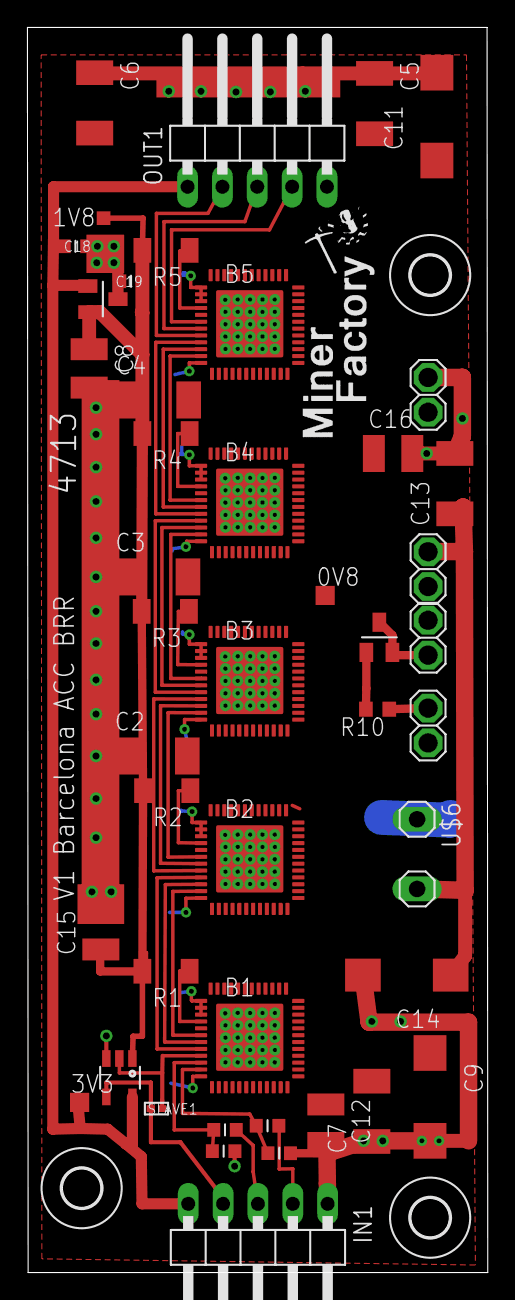
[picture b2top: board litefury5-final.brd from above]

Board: 2 copper layers, 33.5 x 90.8 mm, 46 parts (0 on the bottom side), 33 nets.

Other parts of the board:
H1, H4: MOUNT-HOLE2.8; 2,8
U$37: MINERFACTORY
